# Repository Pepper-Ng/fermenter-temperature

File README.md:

# fermenter-temperature
Temperature controller for beer fermenter

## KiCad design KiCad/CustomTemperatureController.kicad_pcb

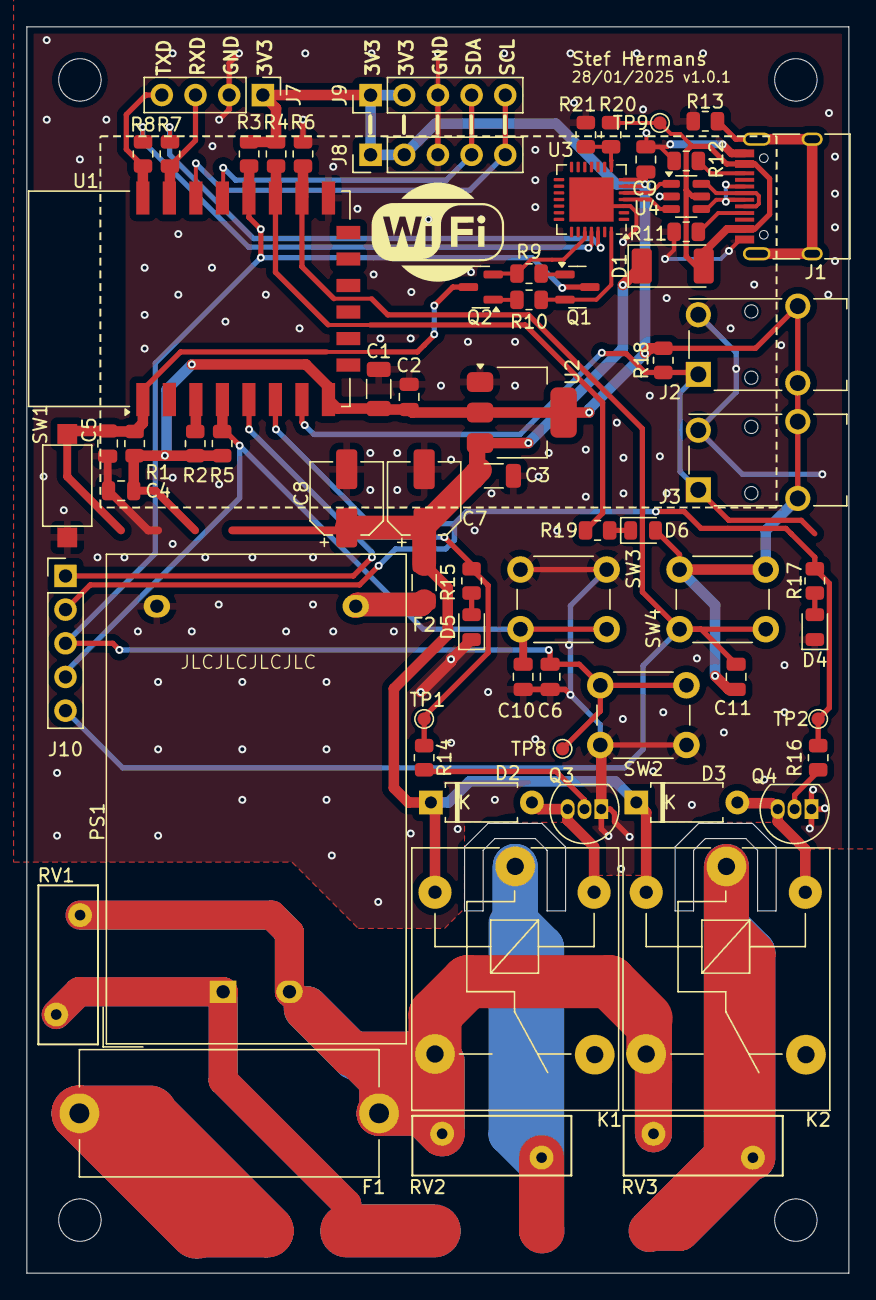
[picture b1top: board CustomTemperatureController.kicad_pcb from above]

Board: 2 copper layers, 62.0 x 94.0 mm, 69 parts (0 on the bottom side), 43 nets.

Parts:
C1, C3: 10uF; C_1206_3216Metric
C2, C5, C6, C10, C11: 100nF; C_0805_2012Metric
C4: 1uF; C_0805_2012Metric
C7: 10uF; CP_Elec_5x5.3
C8: 47uF; CP_Elec_5x5.3
C9: 0.1uF; C_0805_2012Metric
D1: B340; D_2010_5025Metric_Pad1.52x2.65mm_HandSolder
D2, D3: 1N4007; D_A-405_P7.62mm_Horizontal
D4: K2_LED; LED_0805_2012Metric
D5: K1_LED; LED_0805_2012Metric
D6: STATUS; LED_0805_2012Metric
F1: 10A; Fuseholder_Cylinder-5x20mm_Stelvio-Kontek_PTF78_Horizontal_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
F2: 200mA; Fuse_1206_3216Metric
J1: USB_C; USB_C_Receptacle_HRO_TYPE-C-31-M-12
J2: AUX1; Jack_3.5mm_Switronic_ST-005-G_horizontal
J3: AUX2; Jack_3.5mm_Switronic_ST-005-G_horizontal
J7: UART; PinHeader_1x04_P2.54mm_Vertical
J8, J9: I2C; PinHeader_1x05_P2.54mm_Vertical
J10: Aux; PinHeader_1x05_P2.54mm_Vertical
K1, K2: SANYOU_SRD-05VDC; Relay_SPDT_SANYOU_SRD_Series_Form_C
PS1: HLK-PM01; Converter_ACDC_Hi-Link_HLK-PMxx
Q1, Q2: SS8050; SOT-23
Q3, Q4: S8050; TO-92_Inline
R1, R2, R3, R5, R6: 10k; R_0805_2012Metric
R4, R9, R10: 12k; R_0805_2012Metric
R7, R8, R15, R17, R19: 470; R_0805_2012Metric
R11, R12: 5.11k; R_0805_2012Metric
R13: 1M; R_0805_2012Metric
R14, R16: 1k; R_0805_2012Metric
R18: 4.7k; R_0805_2012Metric
R20: 22k; R_0805_2012Metric
R21: 47k; R_0805_2012Metric
RV1, RV2, RV3: 275V; RV_Disc_D12mm_W4.5mm_P7.5mm
SW1: RESET; SW_SPST_CK_RS282G05A3
SW2: FLASH; SW_PUSH_6mm_H13mm
SW3: BTN1; SW_PUSH_6mm_H13mm
SW4: BTN2; SW_PUSH_6mm_H13mm
TP1: K1_TP; TestPoint_Pad_D1.0mm
TP2: K2_TP; TestPoint_Pad_D1.0mm
TP8: GPIO0_TP; TestPoint_Pad_D1.0mm
TP9: VBUS_TP; TestPoint_Pad_D1.0mm
U1: ESP-12E
U2: AMS1117-3.3; SOT-223-3_TabPin2
U3: CP2102N; QFN-28-1EP_5x5mm_P0.5mm_EP3.35x3.35mm
U4: USBLC6-2SC6; SOT-23-6

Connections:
+3V3: C1.1, C2.1, C4.1, C9.1, C11.1, D6.2 (A), J2.T, J3.T, J7.1, J8.1, J8.2, J9.1, J9.2, R1.2, R2.2, R3.2, R4.2, R5.2, R18.2, SW4.2, U1.8 (VCC), U2.2 (VO), U3.6 (VDD), U3.7 (VREGIN)
+5V: C3.1, C7.1, C8.1, D1.1 (K), D2.1 (K), D3.1 (K), F2.2, K1.2, K2.2, U2.3 (VI)
/AC_L_FUSED: F1.2, K1.3, K2.3, PS1.2 (AC/N), RV1.2, RV2.2, RV3.2
/AC_L_K1: K1.1, RV2.1
/AC_L_K2: K2.1, RV3.1
/AC_N: PS1.1 (AC/L), RV1.1
/ESP_1W: J2.R, J3.R, R18.1, U1.7 (GPIO13)
/ESP_EN: R2.1, U1.3 (EN)
/ESP_IO0: C6.1, J10.3, Q1.3 (C), R3.1, SW2.1, TP8.1, U1.18 (GPIO0)
/ESP_IO2: R4.1, R19.1, U1.17 (GPIO2)
/ESP_IO15: C11.2, J10.5, R6.1, SW4.1, U1.16 (GPIO15)
/ESP_IO16: C10.1, J10.4, R5.1, SW3.1, U1.4 (GPIO16)
/ESP_K1: J10.1, R14.2, R15.2, TP1.1, U1.5 (GPIO14)
/ESP_K2: J10.2, R16.2, R17.2, TP2.1, U1.6 (GPIO12)
/ESP_RST: C5.1, Q2.3 (C), R1.1, SW1.1, U1.1 (~RST)
/ESP_RXD: J7.3, R7.2, U1.21 (GPIO3/RXD)
/ESP_SCL: J8.5, J9.5, U1.20 (GPIO5)
/ESP_SDA: J8.4, J9.4, U1.19 (GPIO4)
/ESP_TXD: J7.4, R8.2, U1.22 (GPIO1/TXD)
/USB_D+: J1.A6 (D+), J1.B6 (D+), U4.4 (I/O2)
/USB_D-: J1.A7 (D-), J1.B7 (D-), U4.6 (I/O1)
/V_BUS: D1.2 (A), J1.A4 (VBUS), J1.A9 (VBUS), J1.B4 (VBUS), J1.B9 (VBUS), R20.2, TP9.1, U4.5 (VBUS)
GND: C1.2, C2.2, C3.2, C4.2, C5.2, C6.2, C7.2, C8.2, C9.2, C10.2, D4.1 (K), D5.1 (K), J1.A1 (GND), J1.A12 (GND), J1.B1 (GND), J1.B12 (GND), J2.S, J3.S, J7.2, J8.3, J9.3, PS1.3 (-Vout), Q3.1 (E), Q4.1 (E), R6.2, R11.2, R12.2, R13.1, R21.2, SW1.2, SW2.2, SW3.2, U1.15 (GND), U2.1 (GND), U3.3 (GND), U3.29 (GND), U4.2 (GND)
unnamed: D2.2 (A), K1.5, Q3.3 (C)
unnamed: D3.2 (A), K2.5, Q4.3 (C)
unnamed: D4.2 (A), R17.1
unnamed: D5.2 (A), R15.1
unnamed: D6.1 (K), R19.2
unnamed: J1.A5 (CC1), R11.1
unnamed: J1.B5 (CC2), R12.1
unnamed: J1.S1 (SHIELD), R13.2
unnamed: F2.1, PS1.4 (+Vout)
unnamed: Q1.1 (B), R9.2
unnamed: Q1.2 (E), R10.1, U3.28 (~DTR)
unnamed: Q2.1 (B), R10.2
unnamed: Q2.2 (E), R9.1, U3.24 (~RTS)
unnamed: Q3.2 (B), R14.1
unnamed: Q4.2 (B), R16.1
unnamed: U3.4 (D+), U4.3 (I/O2)
unnamed: U3.5 (D-), U4.1 (I/O1)
unnamed: R8.1, U3.25 (RXD)
unnamed: R7.1, U3.26 (TXD)
unnamed: R20.1, R21.1, U3.8 (VBUS)

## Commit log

2025-02-28 Add gerbers
2025-02-28 Rev101 add resistors.
2025-02-28 Update revision text on board.
2025-02-28 Add gitignore.
2025-02-28 Add code.
2025-03-01 Add StatusController and RelayController.
2025-03-01 Rename setpoints to configurations, minor fixes.
2025-03-01 Add missing file.
2025-03-06 Add basic WiFi connectivity, add saving setpoints in permanent storage.
